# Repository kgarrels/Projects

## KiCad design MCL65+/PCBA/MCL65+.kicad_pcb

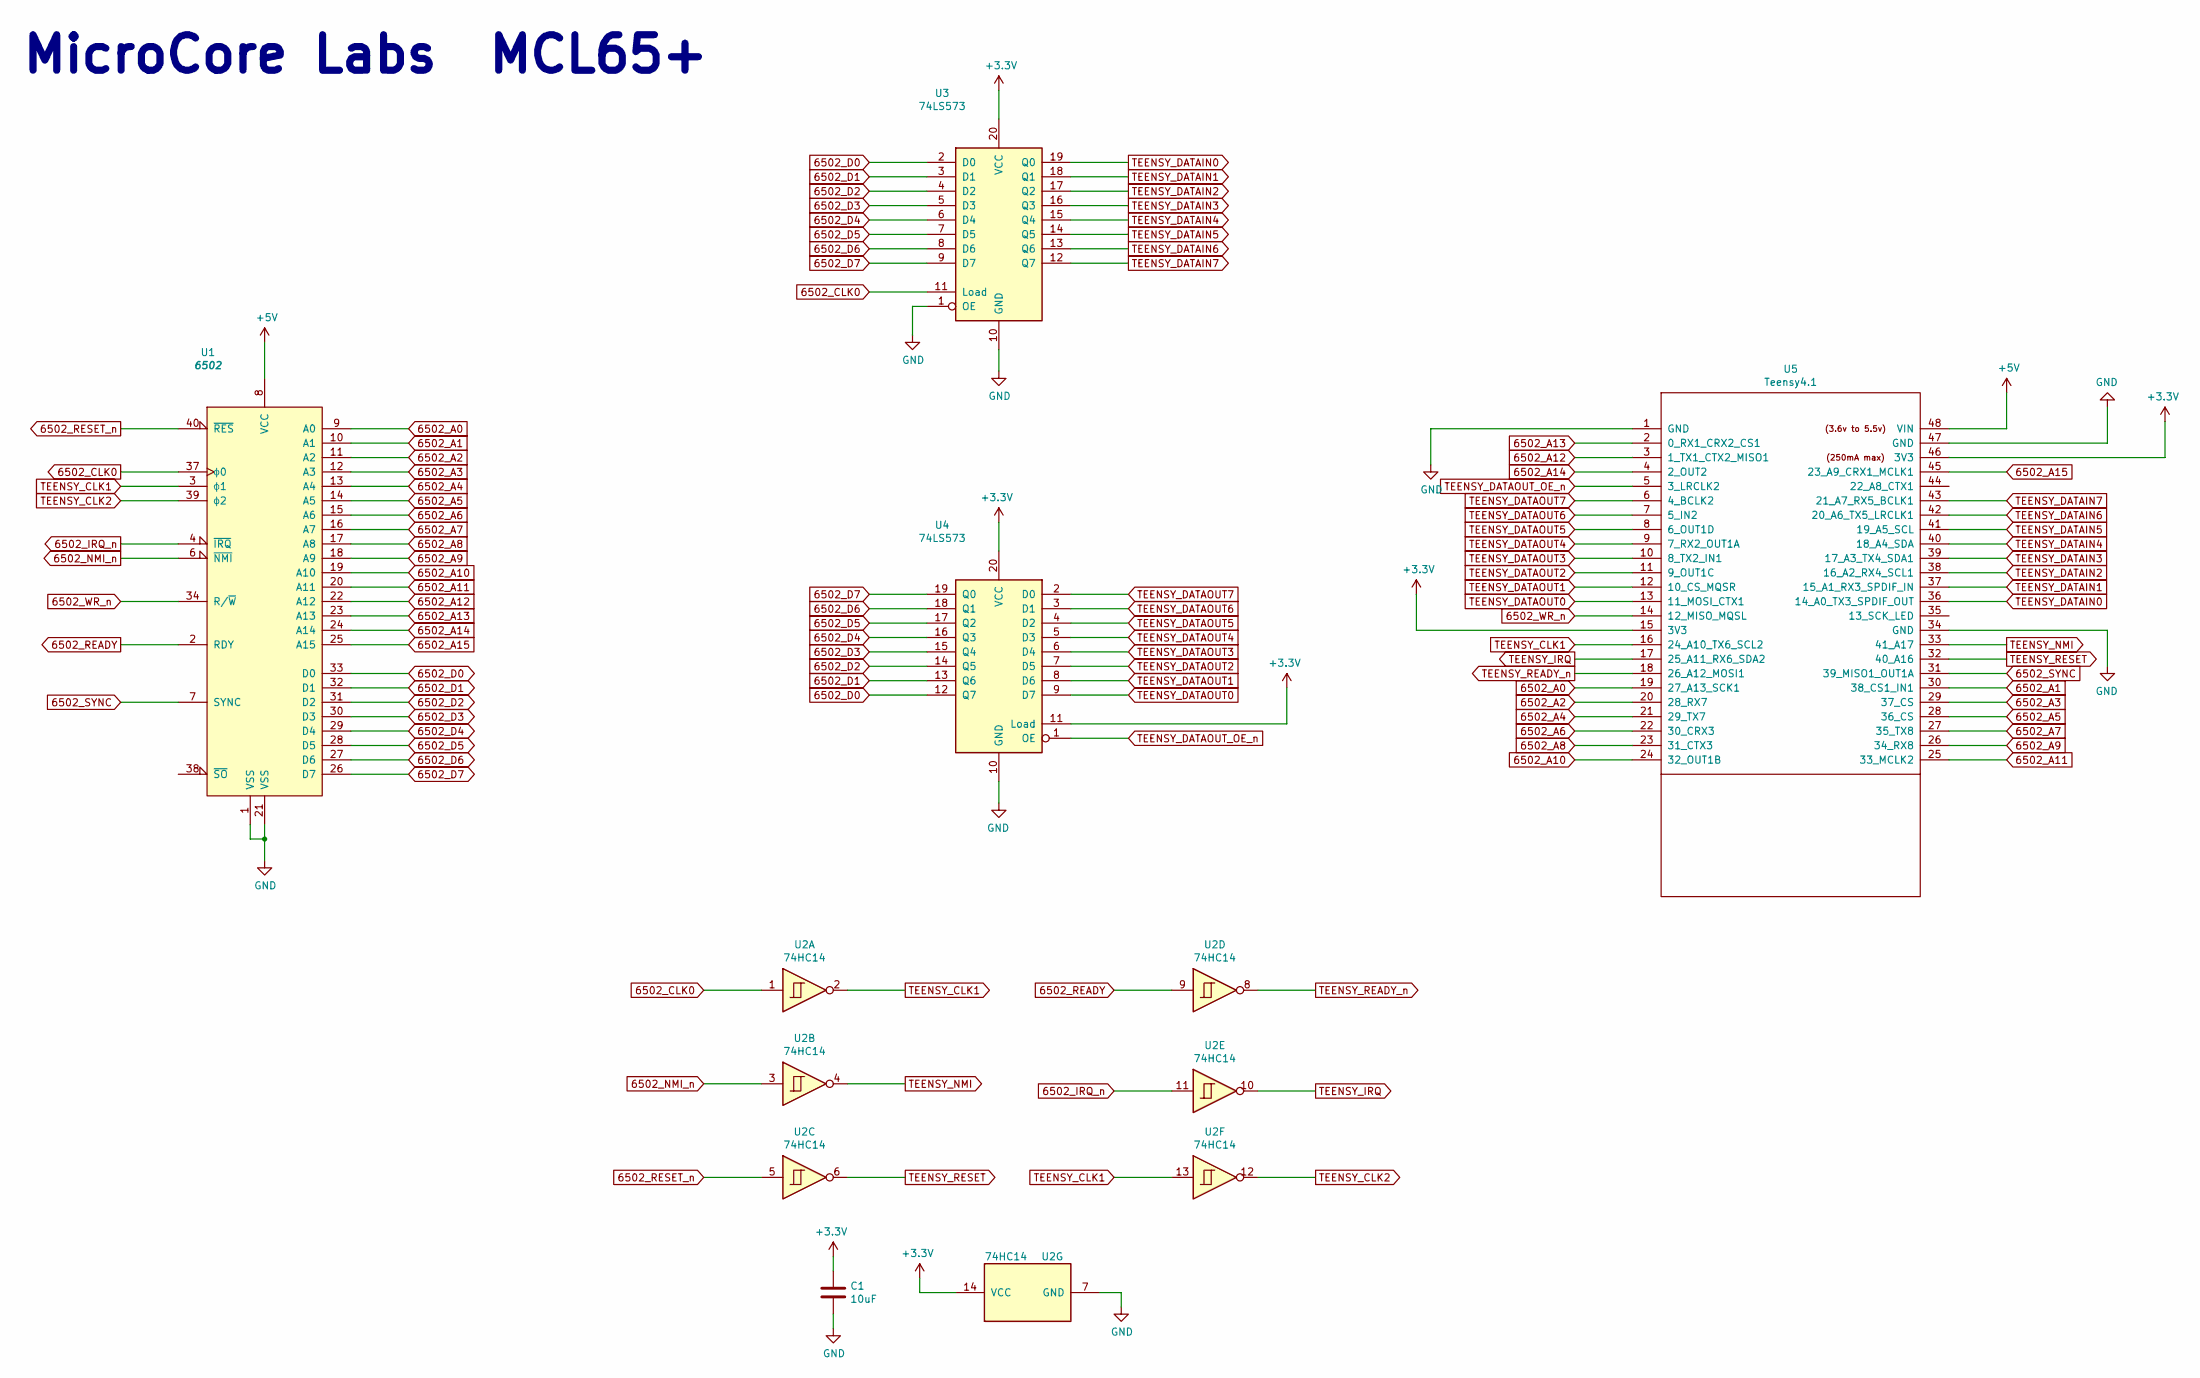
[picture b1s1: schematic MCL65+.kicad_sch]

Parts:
C1: 10uF; C_Disc_D7.0mm_W2.5mm_P5.00mm
U1: 6502; DIP-40_W15.24mm
U2: 74HC14; DIP-14_W7.62mm_Socket
U3, U4: 74LS573; DIP-20_W7.62mm_Socket
U5: Teensy4.1; Teensy41

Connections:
6502_A0: U1.9 (A0), U5.19 (27_A13_SCK1)
6502_A1: U1.10 (A1), U5.30 (38_CS1_IN1)
6502_A2: U1.11 (A2), U5.20 (28_RX7)
6502_A3: U1.12 (A3), U5.29 (37_CS)
6502_A4: U1.13 (A4), U5.21 (29_TX7)
6502_A5: U1.14 (A5), U5.28 (36_CS)
6502_A6: U1.15 (A6), U5.22 (30_CRX3)
6502_A7: U1.16 (A7), U5.27 (35_TX8)
6502_A8: U1.17 (A8), U5.23 (31_CTX3)
6502_A9: U1.18 (A9), U5.26 (34_RX8)
6502_A10: U1.19 (A10), U5.24 (32_OUT1B)
6502_A11: U1.20 (A11), U5.25 (33_MCLK2)
6502_A12: U1.22 (A12), U5.3 (1_TX1_CTX2_MISO1)
6502_A13: U1.23 (A13), U5.2 (0_RX1_CRX2_CS1)
6502_A14: U1.24 (A14), U5.4 (2_OUT2)
6502_A15: U1.25 (A15), U5.45 (23_A9_CRX1_MCLK1)
6502_CLK0: U1.37 (ϕ0), U2.1, U3.11 (Load)
6502_D0: U1.33 (D0), U3.2 (D0), U4.12 (Q7)
6502_D1: U1.32 (D1), U3.3 (D1), U4.13 (Q6)
6502_D2: U1.31 (D2), U3.4 (D2), U4.14 (Q5)
6502_D3: U1.30 (D3), U3.5 (D3), U4.15 (Q4)
6502_D4: U1.29 (D4), U3.6 (D4), U4.16 (Q3)
6502_D5: U1.28 (D5), U3.7 (D5), U4.17 (Q2)
6502_D6: U1.27 (D6), U3.8 (D6), U4.18 (Q1)
6502_D7: U1.26 (D7), U3.9 (D7), U4.19 (Q0)
6502_IRQ_n: U1.4 (~IRQ), U2.11
6502_NMI_n: U1.6 (~NMI), U2.3
6502_READY: U1.2 (RDY), U2.9
6502_RESET_n: U1.40 (~RES), U2.5
6502_SYNC: U1.7 (SYNC), U5.31 (39_MISO1_OUT1A)
6502_WR_n: U1.34 (R/~W), U5.14 (12_MISO_MQSL)
+3V3: C1.1, U2.14 (VCC), U3.20 (VCC), U4.11 (Load), U4.20 (VCC), U5.15 (3V3), U5.46 (3V3)
+5V: U1.8 (VCC), U5.48 (VIN)
GND: C1.2, U1.1 (VSS), U1.21 (VSS), U2.7 (GND), U3.1 (OE), U3.10 (GND), U4.10 (GND), U5.1 (GND), U5.34 (GND), U5.47 (GND)
TEENSY_CLK1: U1.3 (ϕ1), U2.2, U2.13, U5.16 (24_A10_TX6_SCL2)
TEENSY_CLK2: U1.39 (ϕ2), U2.12
TEENSY_DATAIN0: U3.19 (Q0), U5.36 (14_A0_TX3_SPDIF_OUT)
TEENSY_DATAIN1: U3.18 (Q1), U5.37 (15_A1_RX3_SPDIF_IN)
TEENSY_DATAIN2: U3.17 (Q2), U5.38 (16_A2_RX4_SCL1)
TEENSY_DATAIN3: U3.16 (Q3), U5.39 (17_A3_TX4_SDA1)
TEENSY_DATAIN4: U3.15 (Q4), U5.40 (18_A4_SDA)
TEENSY_DATAIN5: U3.14 (Q5), U5.41 (19_A5_SCL)
TEENSY_DATAIN6: U3.13 (Q6), U5.42 (20_A6_TX5_LRCLK1)
TEENSY_DATAIN7: U3.12 (Q7), U5.43 (21_A7_RX5_BCLK1)
TEENSY_DATAOUT0: U4.9 (D7), U5.13 (11_MOSI_CTX1)
TEENSY_DATAOUT1: U4.8 (D6), U5.12 (10_CS_MQSR)
TEENSY_DATAOUT2: U4.7 (D5), U5.11 (9_OUT1C)
TEENSY_DATAOUT3: U4.6 (D4), U5.10 (8_TX2_IN1)
TEENSY_DATAOUT4: U4.5 (D3), U5.9 (7_RX2_OUT1A)
TEENSY_DATAOUT5: U4.4 (D2), U5.8 (6_OUT1D)
TEENSY_DATAOUT6: U4.3 (D1), U5.7 (5_IN2)
TEENSY_DATAOUT7: U4.2 (D0), U5.6 (4_BCLK2)
TEENSY_DATAOUT_OE_n: U4.1 (OE), U5.5 (3_LRCLK2)
TEENSY_IRQ: U2.10, U5.17 (25_A11_RX6_SDA2)
TEENSY_NMI: U2.4, U5.33 (41_A17)
TEENSY_READY_n: U2.8, U5.18 (26_A12_MOSI1)
TEENSY_RESET: U2.6, U5.32 (40_A16)

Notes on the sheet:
MicroCore Labs MCL65+

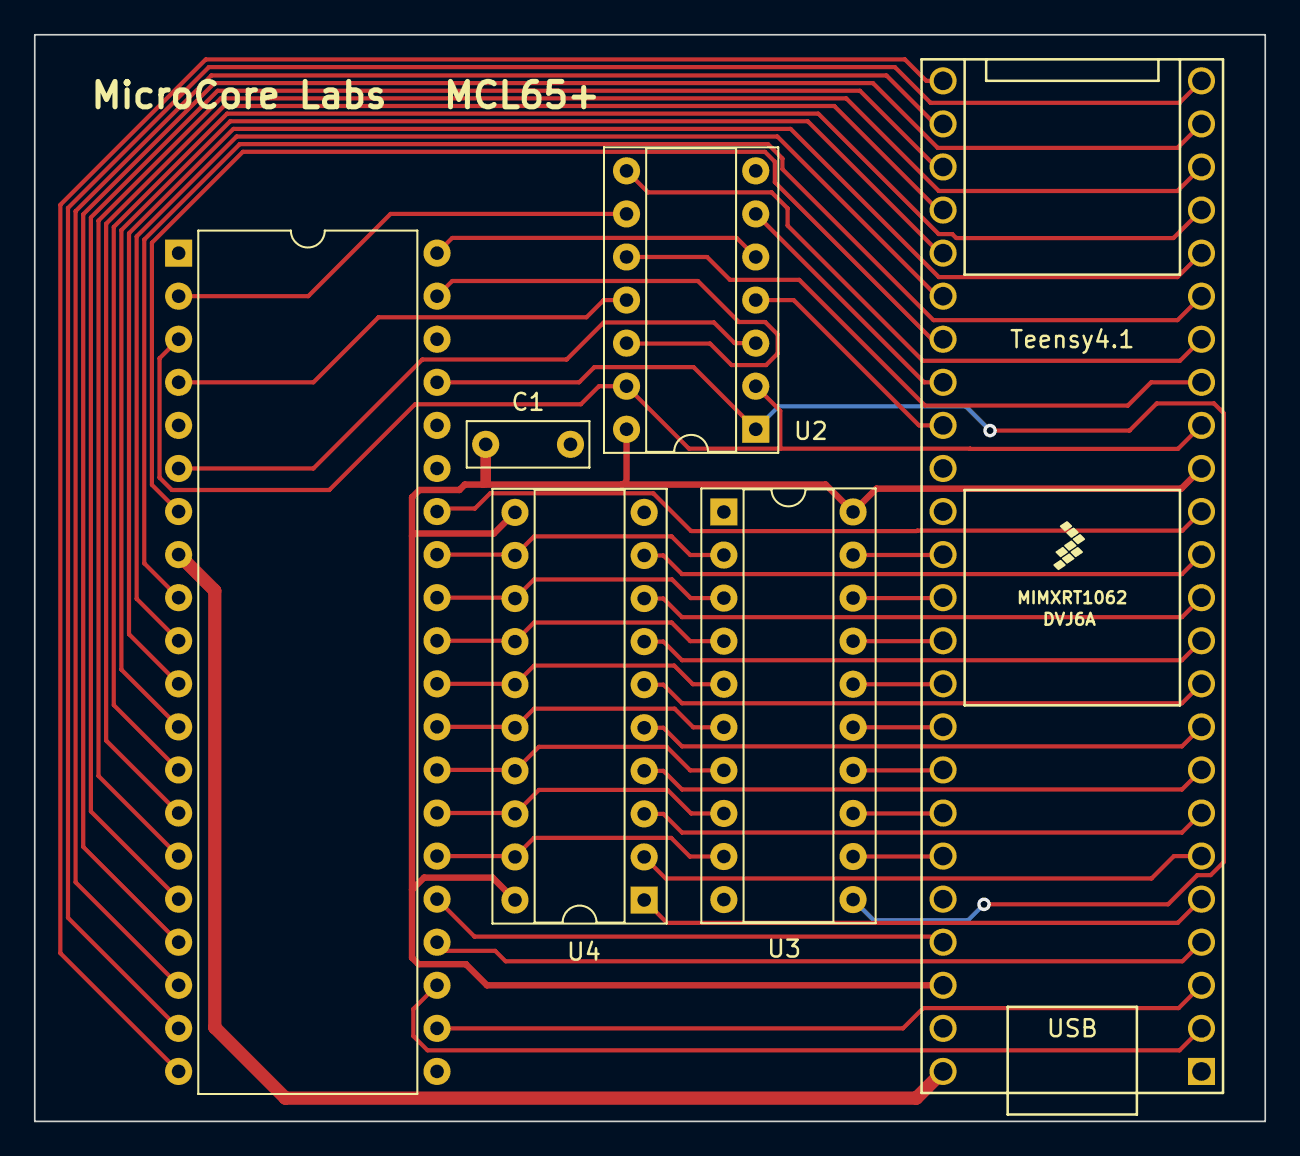
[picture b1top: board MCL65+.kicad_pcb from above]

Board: 2 copper layers, 72.6 x 64.1 mm, 6 parts (0 on the bottom side), 57 nets.

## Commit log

2023-05-14 modifications for PET 2001N
